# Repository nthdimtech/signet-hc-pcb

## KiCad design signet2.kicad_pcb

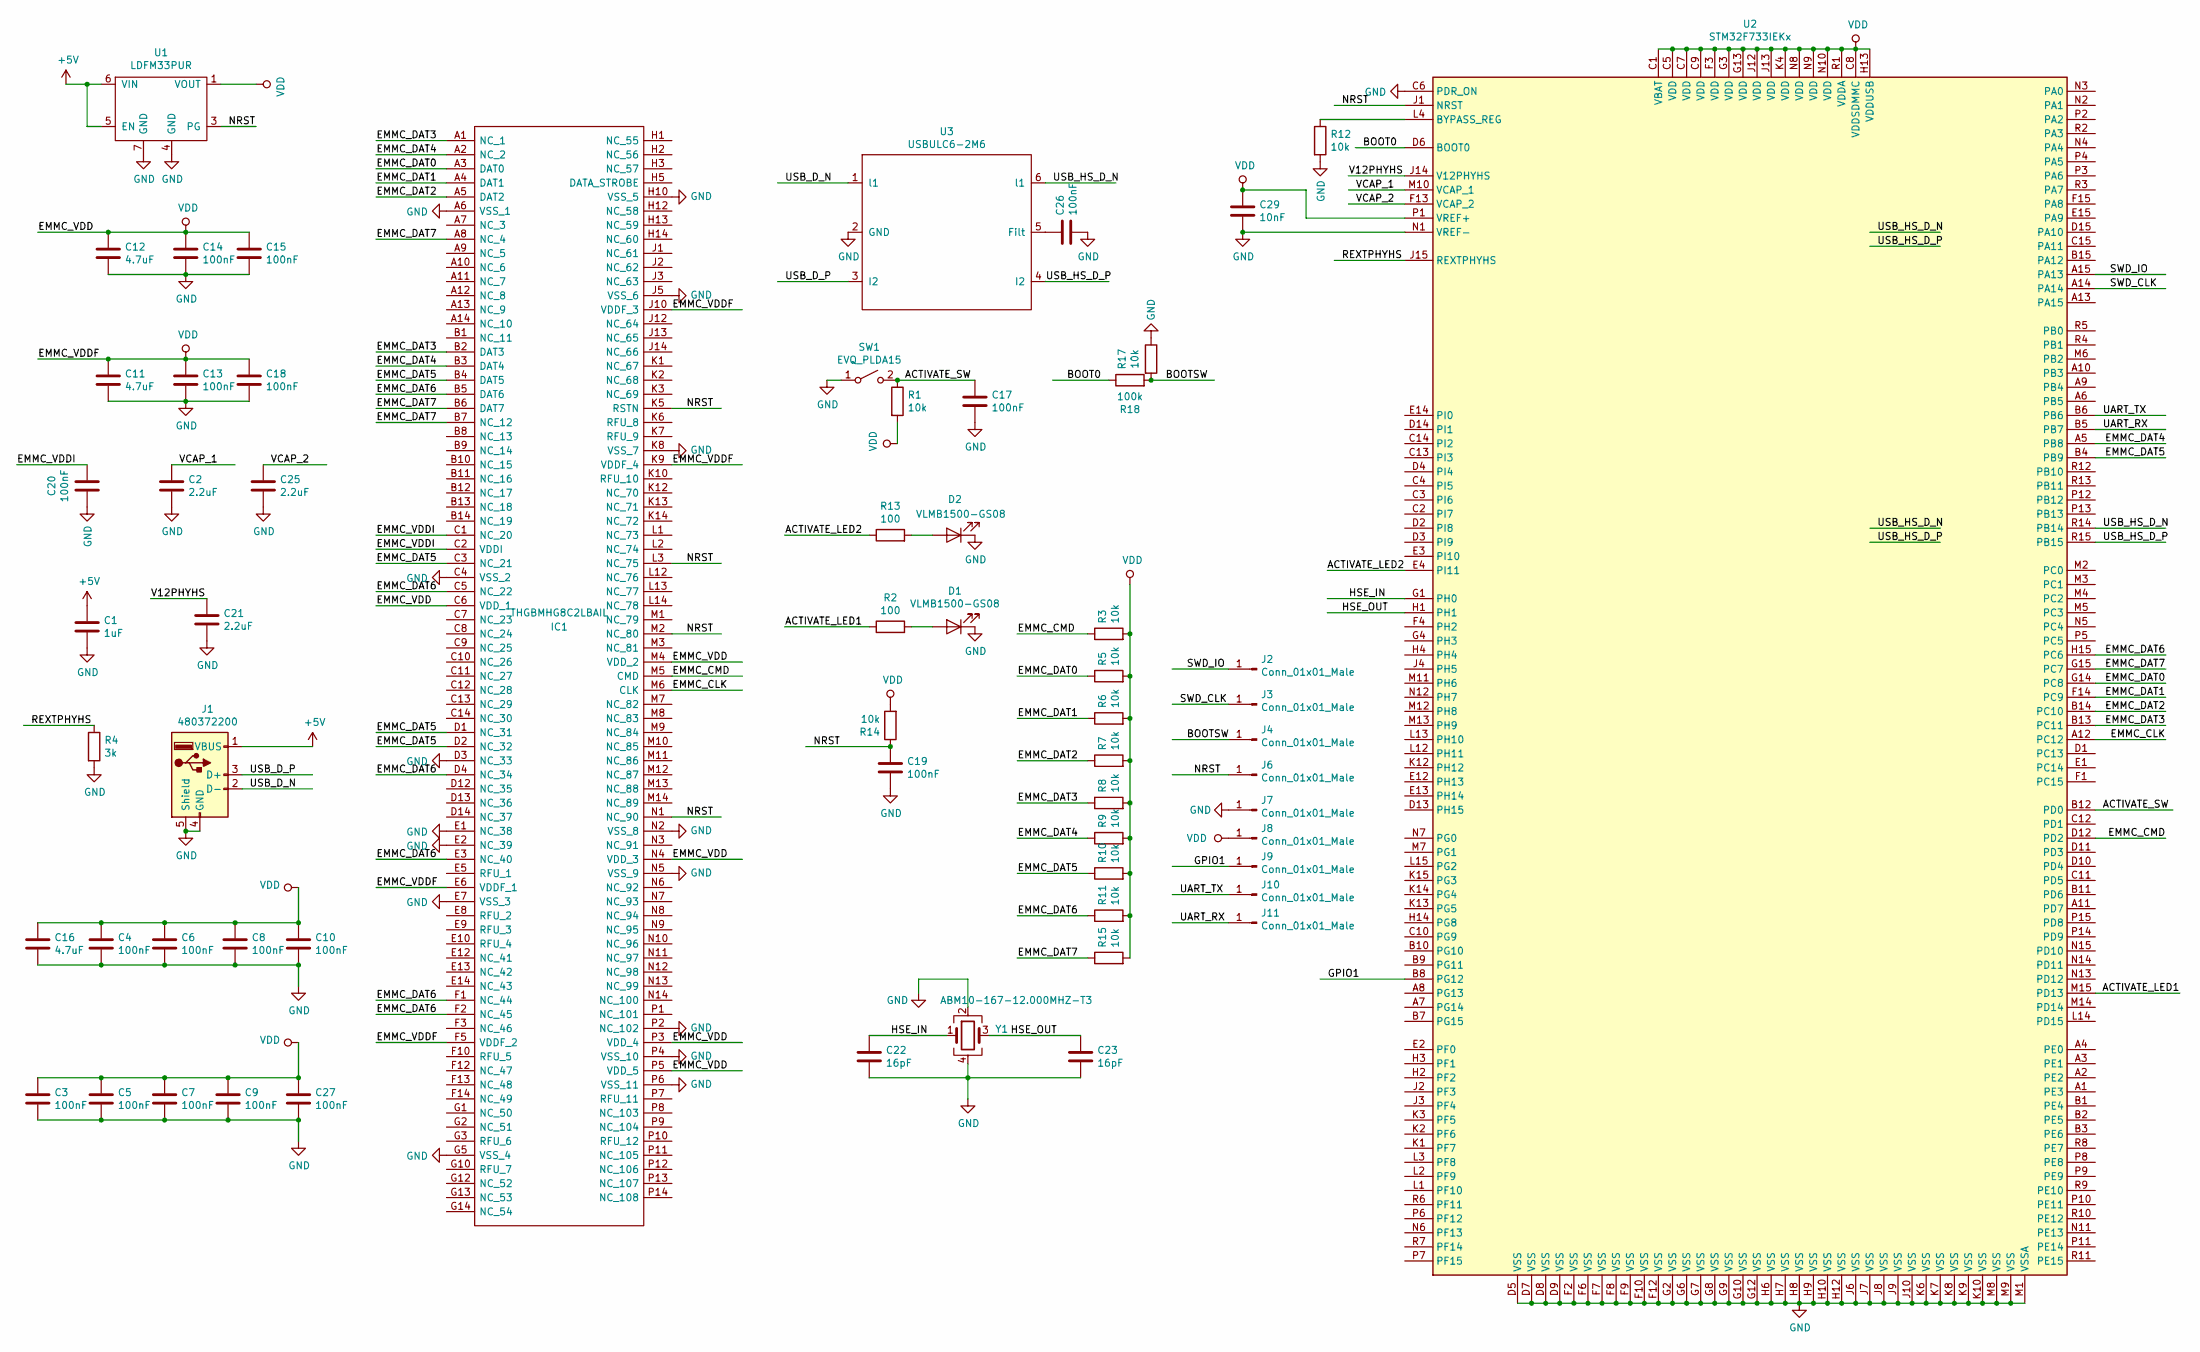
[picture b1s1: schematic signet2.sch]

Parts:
C1: 1uF; C_0402_1005Metric
C2, C21, C25: 2.2uF; C_0402_1005Metric
C3, C4, C5, C6, C7, C8, C9, C10, C13, C14, C15, C17, C18, C19, C20, C26, C27: 100nF; C_0201_0603Metric
C11, C12, C16: 4.7uF; C_0402_1005Metric
C22, C23: 16pF; C_0402_1005Metric
C29: 10nF; R_0201_0603Metric
D1, D2: VLMB1500-GS08; D_0402_1005Metric
IC1: THGBMHG8C2LBAIL; FBGA153
J1: 480372200; MOLEX-480037-2200
J2, J3, J4, J6, J7, J8, J9, J10, J11: Conn_01x01_Male; TestPoint_Pad_1.5x1.5mm
R1, R3, R5, R6, R7, R8, R9, R10, R11, R12, R14, R15, R17: 10k; R_0201_0603Metric
R2, R13: 100; R_0402_1005Metric
R4: 3k; R_0201_0603Metric
R18: 100k; R_0201_0603Metric
SW1: EVQ_PLDA15; SW_SPST_Panasonic_EVQPL_3PL_5PL_PT_A15
U1: LDFM33PUR; VDFN6
U2: STM32F733IEKx; UFBGA-201_10x10mm_Layout15x15_P0.65mm
U3: USBULC6-2M6; ST_UQFN-6L_1.5x1.7mm_Pitch0.5mm
Y1: ABM10-167-12.000MHZ-T3; Crystal_SMD_2520-4Pin_2.5x2.0mm

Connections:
+5V: C1.1, J1.1 (VBUS), U1.5 (EN), U1.6 (VIN)
/ACTIVATE_LED1: R2.1, U2.M15 (PD13)
/ACTIVATE_LED2: R13.1, U2.E4 (PI11)
/ACTIVATE_SW: C17.1, R1.1, SW1.2 (B), U2.B12 (PD0)
/BOOT0: R18.1, U2.D6 (BOOT0)
/BOOTSW: J4.1, R17.2, R18.2
/EMMC_CLK: IC1.M6 (CLK), U2.A12 (PC12)
/EMMC_CMD: IC1.M5 (CMD), R3.1, U2.D12 (PD2)
/EMMC_DAT0: IC1.A3 (DAT0), R5.1, U2.G14 (PC8)
/EMMC_DAT1: IC1.A4 (DAT1), R6.1, U2.F14 (PC9)
/EMMC_DAT2: IC1.A5 (DAT2), R7.1, U2.B14 (PC10)
/EMMC_DAT3: IC1.A1 (NC_1), IC1.B2 (DAT3), R8.1, U2.B13 (PC11)
/EMMC_DAT4: IC1.A2 (NC_2), IC1.B3 (DAT4), R9.1, U2.A5 (PB8)
/EMMC_DAT5: IC1.B4 (DAT5), IC1.C3 (NC_21), IC1.D1 (NC_31), IC1.D2 (NC_32), R10.1, U2.B4 (PB9)
/EMMC_DAT6: IC1.B5 (DAT6), IC1.C5 (NC_22), IC1.D4 (NC_34), IC1.E3 (NC_40), IC1.F1 (NC_44), IC1.F2 (NC_45), R11.1, U2.H15 (PC6)
/EMMC_DAT7: IC1.A8 (NC_4), IC1.B6 (DAT7), IC1.B7 (NC_12), R15.1, U2.G15 (PC7)
/EMMC_VDDI: C20.1, IC1.C1 (NC_20), IC1.C2 (VDDI)
/GPIO1: J9.1, U2.B8 (PG12)
/HSE_IN: C22.1, U2.G1 (PH0), Y1.1
/HSE_OUT: C23.1, U2.H1, Y1.3
/NRST: C19.1, IC1.K5 (RSTN), IC1.L3 (NC_75), IC1.M2 (NC_80), IC1.N1 (NC_90), J6.1, R14.1, U1.3 (PG), U2.J1 (NRST)
/REXTPHYHS: R4.1, U2.J15 (REXTPHYHS)
/SWD_CLK: J3.1, U2.A14
/SWD_IO: J2.1, U2.A15 (PA13)
/UART_RX: J11.1, U2.B5 (PB7)
/UART_TX: J10.1, U2.B6
/USB_D_N: J1.2 (D-), U3.1 (l1)
/USB_D_P: J1.3 (D+), U3.3 (I2)
/USB_HS_D_N: U2.R14 (PB14), U3.6 (l1)
/USB_HS_D_P: U2.R15 (PB15), U3.4 (I2)
/V12PHYHS: C21.1, U2.J14 (V12PHYHS)
/VCAP_1: C2.1, U2.M10 (VCAP_1)
/VCAP_2: C25.1, U2.F13 (VCAP_2)
GND: C1.2, C2.2, C3.2, C4.2, C5.2, C6.2, C7.2, C8.2, C9.2, C10.2, C11.2, C12.2, C13.2, C14.2, C15.2, C16.2, C17.2, C18.2, C19.2, C20.2, C21.2, C22.2, C23.2, C25.2, C26.2, C27.2, C29.2, D1.1 (K), D2.1 (K), IC1.A6 (VSS_1), IC1.C4 (VSS_2), IC1.D3 (NC_33), IC1.E1 (NC_38), IC1.E2 (NC_39), IC1.E7 (VSS_3), IC1.G5 (VSS_4), IC1.H10 (VSS_5), IC1.J5 (VSS_6), IC1.K8 (VSS_7), IC1.N2 (VSS_8), IC1.N5 (VSS_9), IC1.P2 (NC_102), IC1.P4 (VSS_10), IC1.P6 (VSS_11), J1.4 (GND), J1.5 (Shield), J7.1, R4.2, R12.2, R17.1, SW1.1 (A), U1.4 (GND), U1.7 (GND), U2.C6 (PDR_ON), U2.D5 (VSS), U2.D7 (VSS), U2.D8 (VSS), U2.D9 (VSS), U2.F2 (VSS), U2.F6 (VSS), U2.F7 (VSS), U2.F8 (VSS), U2.F9 (VSS), U2.F10 (VSS), U2.F12 (VSS), U2.G2 (VSS), U2.G6 (VSS), U2.G7 (VSS), U2.G8 (VSS), U2.G9 (VSS), U2.G10 (VSS), U2.G12 (VSS), U2.H6 (VSS), U2.H7 (VSS), U2.H8 (VSS), U2.H9 (VSS), U2.H10 (VSS), U2.H12 (VSS), U2.J6 (VSS), U2.J7 (VSS), U2.J8 (VSS), U2.J9 (VSS), U2.J10 (VSS), U2.K6 (VSS), U2.K7 (VSS), U2.K8 (VSS), U2.K9 (VSS), U2.K10 (VSS), U2.M1 (VSSA), U2.M8 (VSS), U2.M9 (VSS), U2.N1 (VREF-), U3.2 (GND), Y1.2, Y1.4
unnamed: C26.1, U3.5 (Filt)
unnamed: D1.2 (A), R2.2
unnamed: D2.2 (A), R13.2
unnamed: R12.1, U2.L4 (BYPASS_REG)
VDD: C3.1, C4.1, C5.1, C6.1, C7.1, C8.1, C9.1, C10.1, C11.1, C12.1, C13.1, C14.1, C15.1, C16.1, C18.1, C27.1, C29.1, IC1.C6 (VDD_1), IC1.E6 (VDDF_1), IC1.F5 (VDDF_2), IC1.J10 (VDDF_3), IC1.K9 (VDDF_4), IC1.M4 (VDD_2), IC1.N4 (VDD_3), IC1.P3 (VDD_4), IC1.P5 (VDD_5), J8.1, R1.2, R3.2, R5.2, R6.2, R7.2, R8.2, R9.2, R10.2, R11.2, R14.2, R15.2, U1.1 (VOUT), U2.C1 (VBAT), U2.C5 (VDD), U2.C7 (VDD), U2.C8 (VDDSDMMC), U2.C9 (VDD), U2.F3 (VDD), U2.G3 (VDD), U2.G13 (VDD), U2.H13 (VDDUSB), U2.J12 (VDD), U2.J13 (VDD), U2.K4 (VDD), U2.N8 (VDD), U2.N9 (VDD), U2.N10 (VDD), U2.P1 (VREF+), U2.R1 (VDDA)

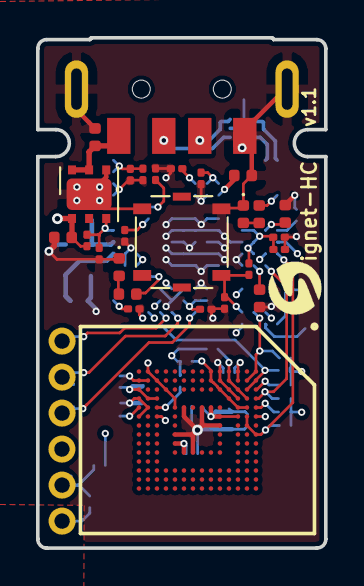
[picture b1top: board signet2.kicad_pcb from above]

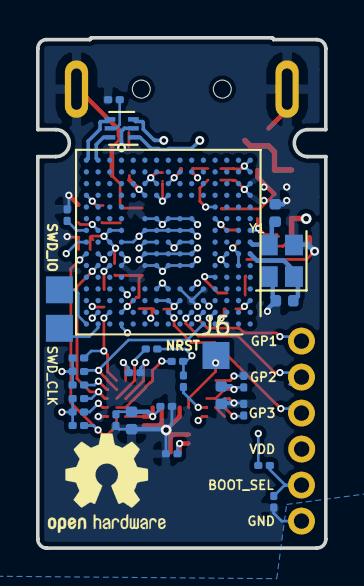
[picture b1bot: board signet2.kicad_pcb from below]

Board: 6 copper layers, 16.0 x 28.3 mm, 62 parts (35 on the bottom side), 39 nets.

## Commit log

2019-09-12 Add CERN OHL v1.2 license
2019-09-13 Thermal and mechanical improvements
    - Change user header to round through hole pads
    - Remove most GND pour areas around user header GND pin so it is easier
    to heat and solder/desolder
    - Tighten fit of USB connector mounting slots
    - Reduce the size of the increased thickness area at USB connector
2019-09-22 Version 1.22
    - Add GND plane pour to GND line through-hole connection
    - Change visual layout in schematic (connections are the same)
    - Make area sticking out near USB port smaller. Needed to take into
    consideration the possible need for the port to be able to bend
    slightly down to fit in enclosure. This will depend on the exact PCB
    thickness and how the USB port seats on it.
